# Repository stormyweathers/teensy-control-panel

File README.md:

# Teensy Control Panel

This project consists of a PCB and arduino library that together provide various I/O capabilities for the teensy 4.0

## PCB Features
    * All jst connectors are in the XH series, except the stemma-QT connectors, which are JST-PH
    * 2x RJ45 ports, each with 4-channel GPIO capability
    * 1x JST 5-pin connector for rotary encoder
    * 8x JST 3-pin connectors for potentiometer analog inputs
    * 3x JST 2-pin connectors for switches or buttons
    * 1x JST 2-pin connector to expose the programming pin if necessary
    * 2x Stemma-QT connectors for I2C comms
        * One of these is intended to be used for an OLED screen 

## Control code features

I've only used this project for myself so far, so the documentation is sparse.
If you're interested, please reach out and I'll use that as motivation to write more clearly.

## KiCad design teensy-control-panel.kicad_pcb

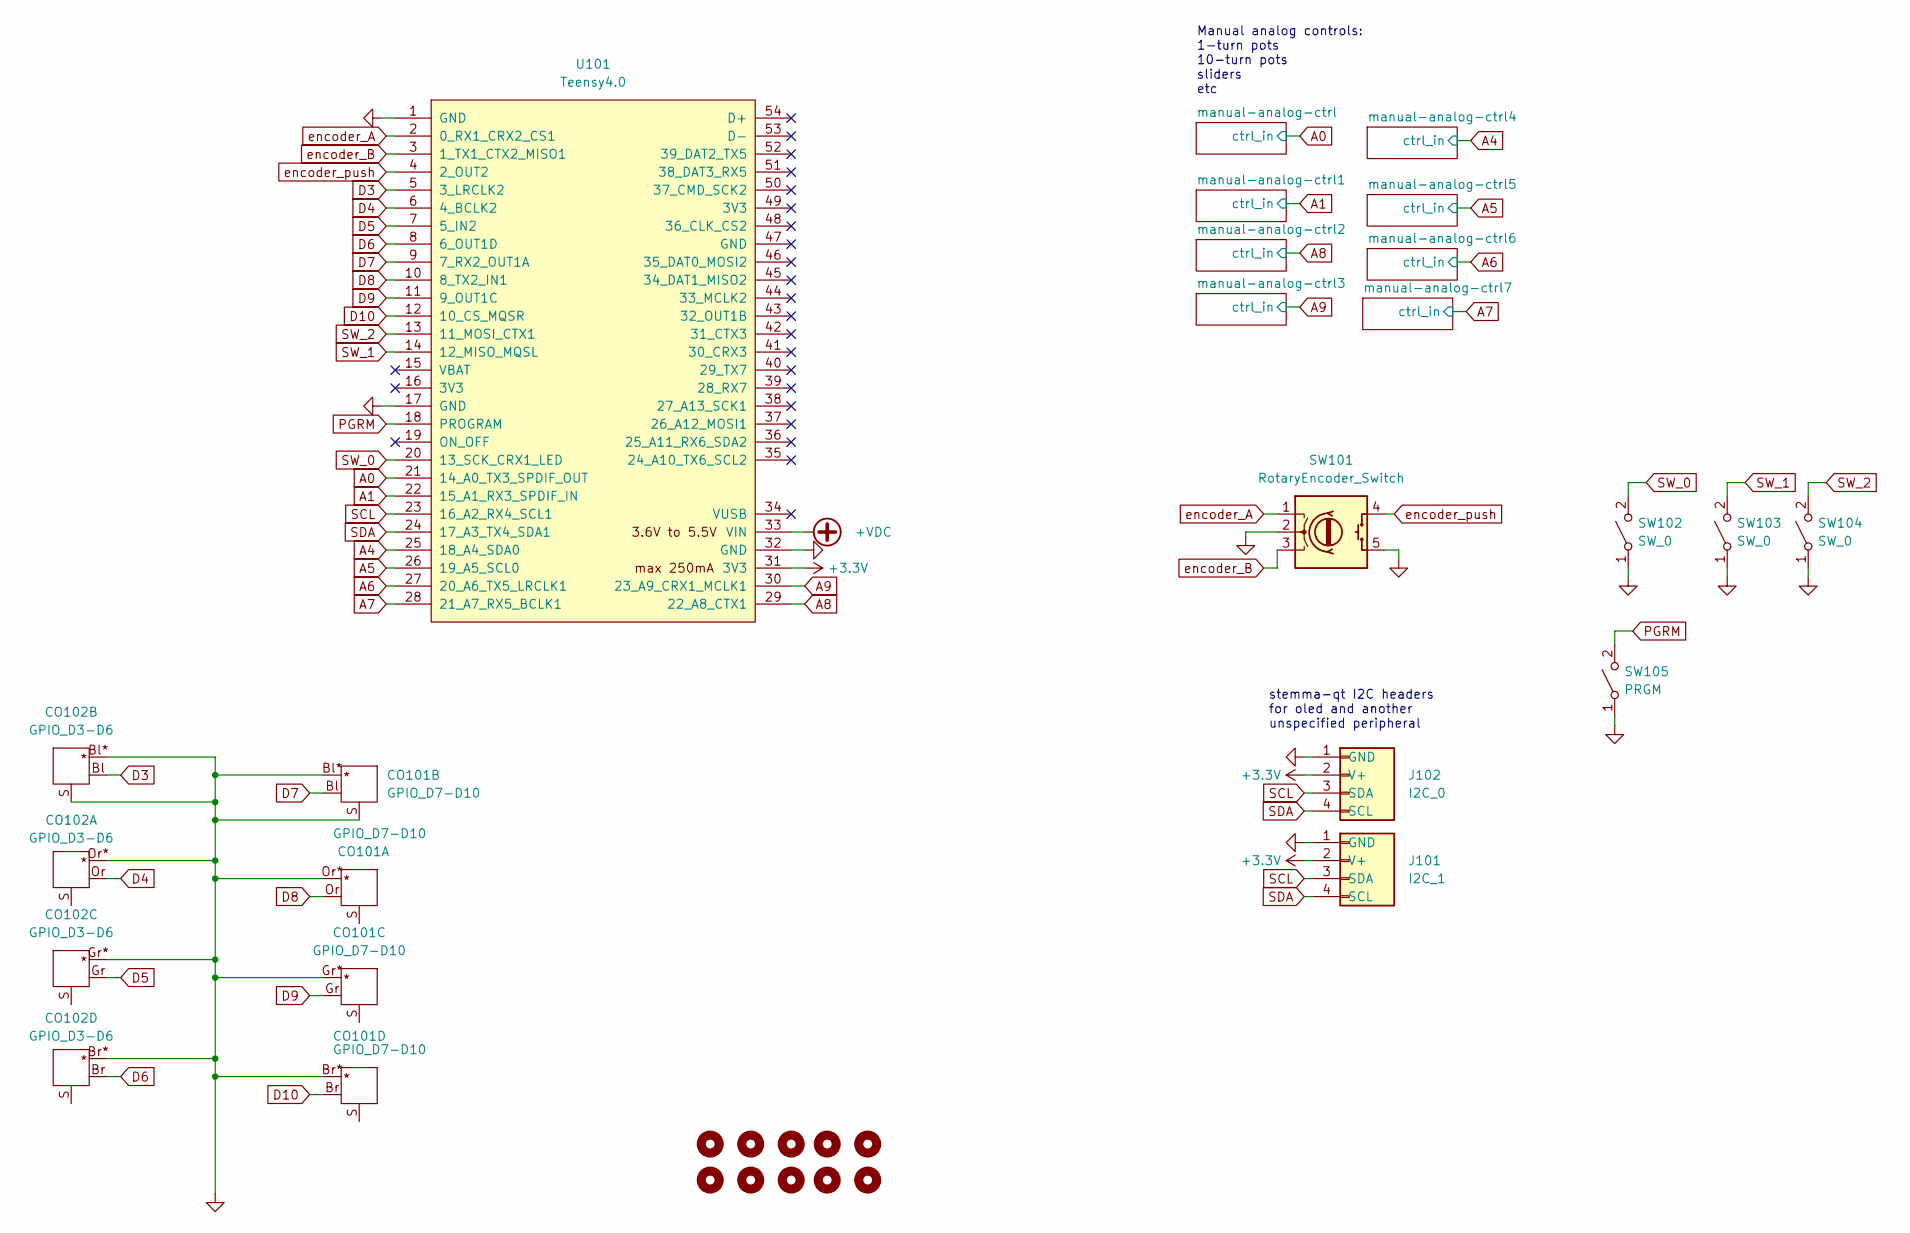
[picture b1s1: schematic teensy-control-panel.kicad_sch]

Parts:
CO101: GPIO_D7-D10; RJ45
CO102: GPIO_D3-D6; RJ45
H101, H102, H103, H104, H105, H106, H107, H108, H109, H110: MountingHole; MountingHole_3.2mm_M3
J101: I2C_1; JST_SH_SM04B-SRSS-TB_1x04-1MP_P1.00mm_Horizontal; jlcpcb C160404
J102: I2C_0; JST_SH_SM04B-SRSS-TB_1x04-1MP_P1.00mm_Horizontal; jlcpcb C160404
SW101: RotaryEncoder_Switch; JST_PH_B5B-PH-SM4-TB_1x05-1MP_P2.00mm_Vertical; jlcpcb C265086
SW102, SW103, SW104: SW_0; JST_PH_B2B-PH-SM4-TB_1x02-1MP_P2.00mm_Vertical; jlcpcb C265003
SW105: PRGM; JST_PH_B2B-PH-SM4-TB_1x02-1MP_P2.00mm_Vertical; jlcpcb C265003
U101: Teensy4.0; Teensy40_reduced

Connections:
+3.3V: J101.2 (V+), J102.2 (V+), U101.31 (3V3); also elsewhere on the board
+VDC: U101.33 (VIN)
A0: U101.21 (14_A0_TX3_SPDIF_OUT); also elsewhere on the board
A1: U101.22 (15_A1_RX3_SPDIF_IN); also elsewhere on the board
A4: U101.25 (18_A4_SDA0); also elsewhere on the board
A5: U101.26 (19_A5_SCL0); also elsewhere on the board
A6: U101.27 (20_A6_TX5_LRCLK1); also elsewhere on the board
A7: U101.28 (21_A7_RX5_BCLK1); also elsewhere on the board
A8: U101.29 (22_A8_CTX1); also elsewhere on the board
A9: U101.30 (23_A9_CRX1_MCLK1); also elsewhere on the board
D3: CO102.Bl, U101.5 (3_LRCLK2)
D4: CO102.Or, U101.6 (4_BCLK2)
D5: CO102.Gr, U101.7 (5_IN2)
D6: CO102.Br, U101.8 (6_OUT1D)
D7: CO101.Bl, U101.9 (7_RX2_OUT1A)
D8: CO101.Or, U101.10 (8_TX2_IN1)
D9: CO101.Gr, U101.11 (9_OUT1C)
D10: CO101.Br, U101.12 (10_CS_MQSR)
GND: CO101.Bl*, CO101.Br*, CO101.Gr*, CO101.Or*, CO101.S, CO102.Bl*, CO102.Br*, CO102.Gr*, CO102.Or*, CO102.S, J101.1 (GND), J102.1 (GND), SW101.2 (C), SW101.5 (S2), SW102.1 (A), SW103.1 (A), SW104.1 (A), SW105.1 (A), U101.1 (GND), U101.17 (GND), U101.32 (GND); also elsewhere on the board
PGRM: SW105.2 (B), U101.18 (PROGRAM)
SCL: J101.3 (SDA), J102.3 (SDA), U101.23 (16_A2_RX4_SCL1)
SDA: J101.4 (SCL), J102.4 (SCL), U101.24 (17_A3_TX4_SDA1)
SW_0: SW102.2 (B), U101.20 (13_SCK_CRX1_LED)
SW_1: SW103.2 (B), U101.14 (12_MISO_MQSL)
SW_2: SW104.2 (B), U101.13 (11_MOSI_CTX1)
encoder_A: SW101.1 (A), U101.2 (0_RX1_CRX2_CS1)
encoder_B: SW101.3 (B), U101.3 (1_TX1_CTX2_MISO1)
encoder_push: SW101.4 (S1), U101.4 (2_OUT2)

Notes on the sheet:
stemma-qt I2C headers for oled and another unspecified peripheral
Manual analog controls: 1-turn pots 10-turn pots sliders etc

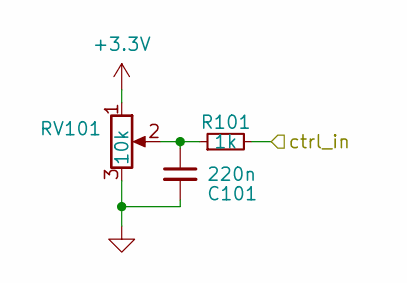
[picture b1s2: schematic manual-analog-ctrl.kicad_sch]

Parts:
C101: 220n; C_0603_1608Metric; jlcpcb C21120
R101: 1k; R_0603_1608Metric; jlcpcb C21190
RV101: 10k; JST_PH_B3B-PH-SM4-TB_1x03-1MP_P2.00mm_Vertical; jlcpcb C265082

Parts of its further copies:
C201, C301, C401, C501, C601, C701, C801, C901: 220n; C_0603_1608Metric; jlcpcb C21120
R201, R301, R401, R501, R601, R701, R801, R901: 1k; R_0603_1608Metric; jlcpcb C21190
RV201, RV301, RV401, RV501, RV601, RV701, RV801, RV901: 10k; JST_PH_B3B-PH-SM4-TB_1x03-1MP_P2.00mm_Vertical; jlcpcb C265082

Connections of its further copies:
+3.3V: RV201.1, RV301.1, RV401.1, RV501.1, RV601.1, RV701.1, RV801.1, RV901.1; also elsewhere on the board
A0: R201.2; also elsewhere on the board
A1: R301.2; also elsewhere on the board
A4: R601.2; also elsewhere on the board
A5: R701.2; also elsewhere on the board
A6: R901.2; also elsewhere on the board
A7: R801.2; also elsewhere on the board
A8: R401.2; also elsewhere on the board
A9: R501.2; also elsewhere on the board
GND: C201.2, C301.2, C401.2, C501.2, C601.2, C701.2, C801.2, C901.2, RV201.3, RV301.3, RV401.3, RV501.3, RV601.3, RV701.3, RV801.3, RV901.3; also elsewhere on the board
unnamed: C201.1, R201.1, RV201.2
unnamed: C301.1, R301.1, RV301.2
unnamed: C401.1, R401.1, RV401.2
unnamed: C501.1, R501.1, RV501.2
unnamed: C601.1, R601.1, RV601.2
unnamed: C701.1, R701.1, RV701.2
unnamed: C801.1, R801.1, RV801.2
unnamed: C901.1, R901.1, RV901.2

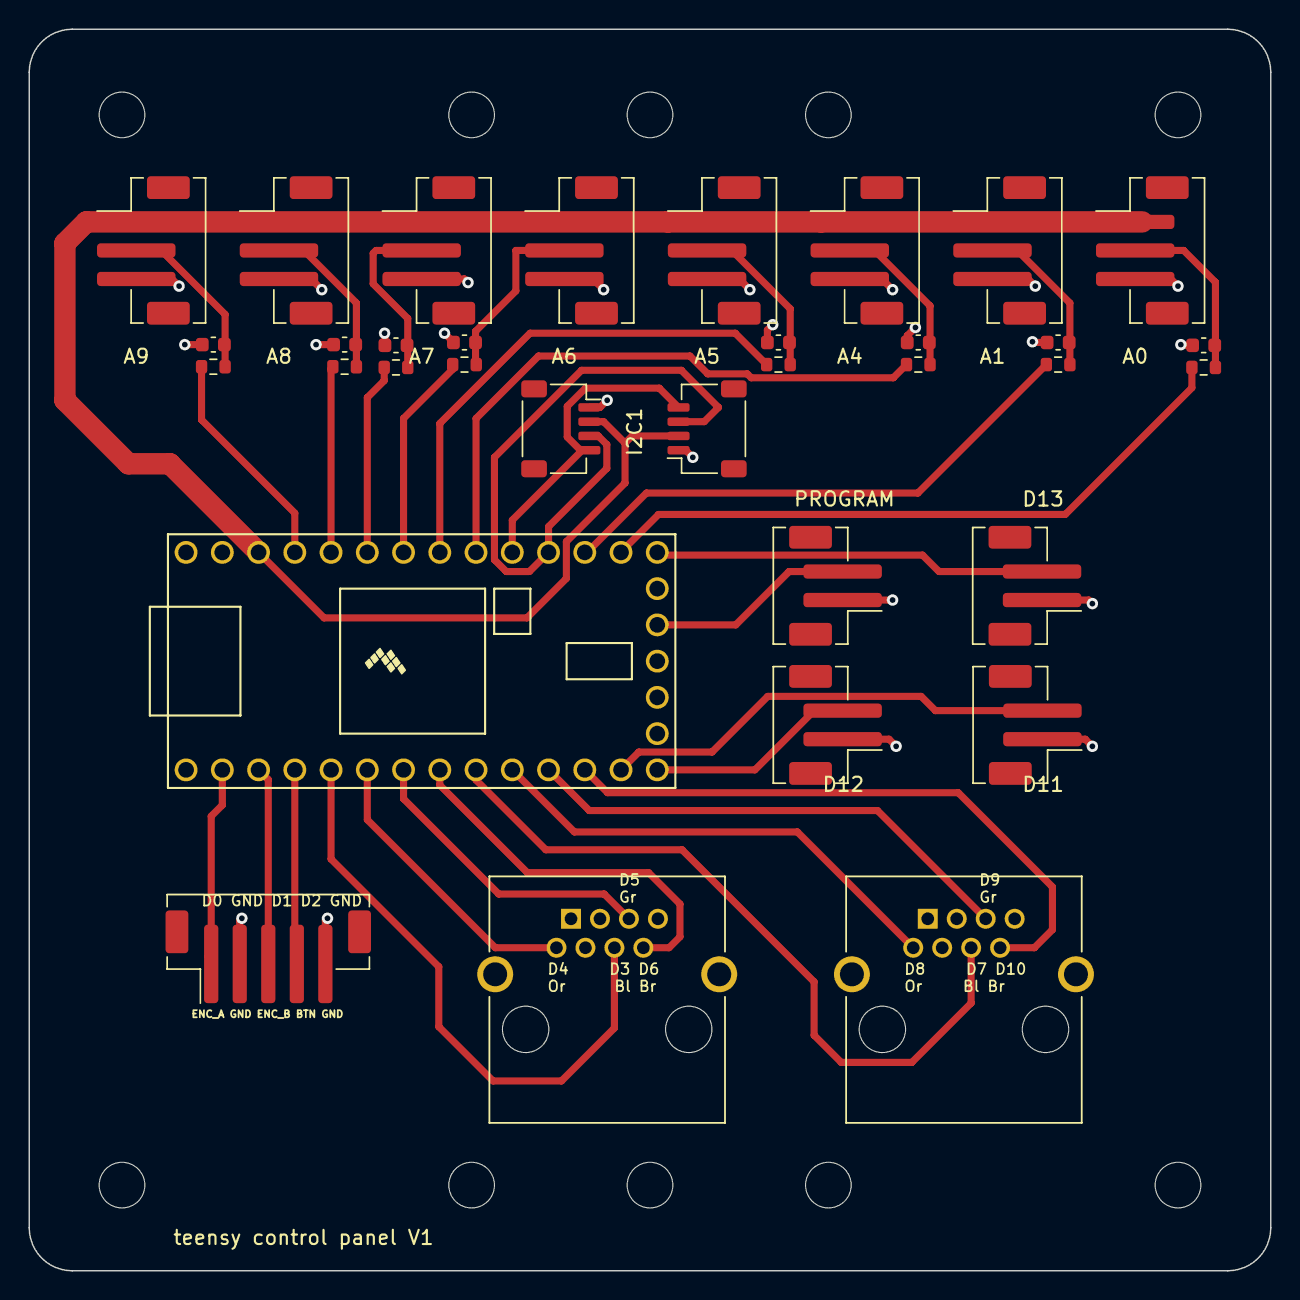
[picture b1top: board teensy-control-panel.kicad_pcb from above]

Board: 2 copper layers, 87.0 x 87.0 mm, 44 parts (0 on the bottom side), 35 nets.

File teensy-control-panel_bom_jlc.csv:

"Comment","Designator","Footprint","LCSC Part #"
"220n","C201,C301,C401,C501,C601,C701,C801,C901","C_0603_1608Metric","C21120"
"I2C_1","J101","JST_SH_SM04B-SRSS-TB_1x04-1MP_P1.00mm_Horizontal","C160404"
"I2C_0","J102","JST_SH_SM04B-SRSS-TB_1x04-1MP_P1.00mm_Horizontal","C160404"
"1k","R201,R301,R401,R501,R601,R701,R801,R901","R_0603_1608Metric","C21190"
"10k","RV201,RV301,RV401,RV501,RV601,RV701,RV801,RV901","JST_PH_B3B-PH-SM4-TB_1x03-1MP_P2.00mm_Vertical","C265082"
"RotaryEncoder_Switch","SW101","JST_PH_B5B-PH-SM4-TB_1x05-1MP_P2.00mm_Vertical","C265086"
"SW_0","SW102,SW103,SW104","JST_PH_B2B-PH-SM4-TB_1x02-1MP_P2.00mm_Vertical","C265003"
"PRGM","SW105","JST_PH_B2B-PH-SM4-TB_1x02-1MP_P2.00mm_Vertical","C265003"

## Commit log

2023-09-07 init commit, V1 ready for fab
2023-09-25 working example of c++ class for reading control panel state
2023-09-25 fixed namespace conflict - digitalWrite
2023-10-02 used debounce library for digital inputs, use OLED for reporting output, use timers for reading inputs
2023-11-05 arduino drier: added joystick float vals with tunable zero point, pins 22/23 (A8/A9) routed to digital IO
2024-03-29 changed case of naming
2024-03-29 added README
2024-03-29 removed backups, tried changing dir structure for includes into platform-io
